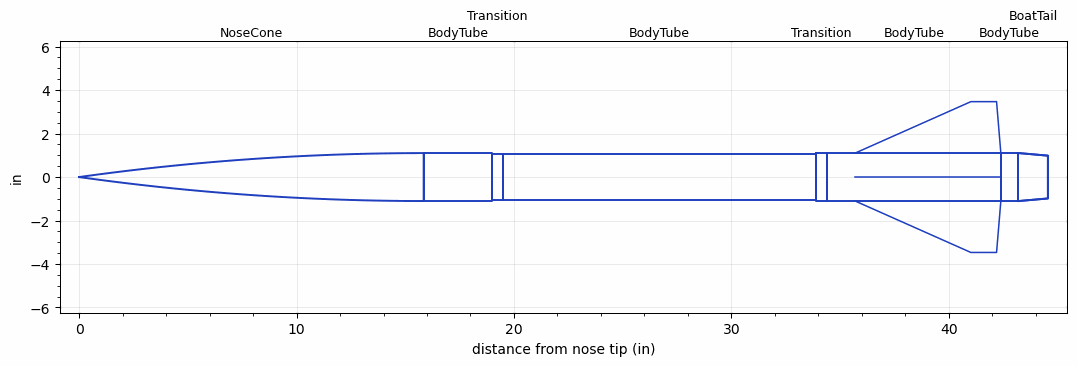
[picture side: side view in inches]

<RASAeroDocument>
 <FileVersion>2</FileVersion>
 <RocketDesign>
  <NoseCone>
   <Length>15.847</Length>
   <Diameter>2.205</Diameter>
   <Shape>Tangent Ogive</Shape>
   <Location>0</Location>
  </NoseCone>
  <BodyTube>
   <Length>3.15</Length>
   <Diameter>2.205</Diameter>
   <Location>15.847</Location>
  </BodyTube>
  <Transition>
   <Length>0.5</Length>
   <Diameter>2.125</Diameter>
   <Location>18.997</Location>
   <RearDiameter>2.125</RearDiameter>
  </Transition>
  <BodyTube>
   <Length>14.4</Length>
   <Diameter>2.125</Diameter>
   <Location>19.497</Location>
  </BodyTube>
  <Transition>
   <Length>0.5</Length>
   <Diameter>2.213</Diameter>
   <Location>33.897</Location>
   <RearDiameter>2.213</RearDiameter>
  </Transition>
  <BodyTube>
   <Length>8</Length>
   <Diameter>2.213</Diameter>
   <Location>34.397</Location>
   <Fin>
    <Count>4</Count>
    <Chord>6.693</Chord>
    <Span>2.362</Span>
    <SweepDistance>5.315</SweepDistance>
    <TipChord>1.181</TipChord>
    <Thickness>0.157</Thickness>
    <LERadius>0.0313</LERadius>
    <Location>6.693</Location>
    <AirfoilSection>Hexagonal</AirfoilSection>
    <FX1>0.5</FX1>
    <FX3>0.5</FX3>
   </Fin>
  </BodyTube>
  <BodyTube>
   <Length>0.787</Length>
   <Diameter>2.213</Diameter>
   <Location>42.397</Location>
   <BoattailLength>1.378</BoattailLength>
   <BoattailRearDiameter>1.969</BoattailRearDiameter>
  </BodyTube>
  <BoatTail>
   <Length>1.378</Length>
   <Diameter>2.213</Diameter>
   <RearDiameter>1.969</RearDiameter>
   <Location>43.184</Location>
  </BoatTail>
  <Surface>Smooth Paint</Surface>
  <ModifiedBarrowman>True</ModifiedBarrowman>
  <Turbulence>True</Turbulence>
  <UseBooster1>False</UseBooster1>
  <UseBooster2>False</UseBooster2>
 </RocketDesign>
 <LaunchSite>
  <Altitude>2000</Altitude>
  <Pressure>29.92</Pressure>
  <RodAngle>0</RodAngle>
  <RodLength>6</RodLength>
  <Temperature>59</Temperature>
  <WindSpeed>4.47</WindSpeed>
 </LaunchSite>
 <Recovery>
  <Altitude1>1000</Altitude1>
  <Altitude2>1000</Altitude2>
  <DeviceType1>None</DeviceType1>
  <DeviceType2>None</DeviceType2>
  <Event1>False</Event1>
  <Event2>False</Event2>
  <Size1>1</Size1>
  <Size2>1</Size2>
  <EventType1>None</EventType1>
  <EventType2>None</EventType2>
  <CD1>1.33</CD1>
  <CD2>1.33</CD2>
 </Recovery>
 <SimulationList>
  <Simulation>
   <SustainerEngine>L444  (Alex)</SustainerEngine>
   <SustainerLaunchWt>7.05</SustainerLaunchWt>
   <SustainerNozzleDiameter>1.2</SustainerNozzleDiameter>
   <SustainerCG>26.81</SustainerCG>
   <SustainerIgnitionDelay>0</SustainerIgnitionDelay>
   <Booster1SeparationDelay>0</Booster1SeparationDelay>
   <Booster1IgnitionDelay>0</Booster1IgnitionDelay>
   <IncludeBooster1>False</IncludeBooster1>
   <Booster2Delay>0</Booster2Delay>
   <IncludeBooster2>False</IncludeBooster2>
   <TimetoApogee>33.19044</TimetoApogee>
   <MaxAltitude>26792.92</MaxAltitude>
   <MaxVelocity>2494.865</MaxVelocity>
   <OptimumWt>7.57875</OptimumWt>
   <OptimumMaxAlt>7.57875</OptimumMaxAlt>
  </Simulation>
 </SimulationList>
</RASAeroDocument>
